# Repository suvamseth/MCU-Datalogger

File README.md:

<div align="center">

# **MCU Datalogger**
### A minimal MCU-based datalogger built in KiCad  

<p>
  <kbd style="padding:3px 14px; font-size:14px; background:#007BFF; color:white;">MCU: ATmega328P-AU</kbd>
  <kbd style="padding:3px 14px; font-size:14px; background:#FF9800; color:white;">RTC: DS3231M</kbd>
  <kbd style="padding:3px 14px; font-size:14px; background:#4CAF50; color:white;">Memory: 24LC1025 × 2</kbd>
  <kbd style="padding:3px 14px; font-size:14px; background:#9C27B0; color:white;">KiCad</kbd>
</p>

</div>

---

## ✨ **Overview**

*A complete KiCad project implementing a simple microcontroller-based datalogger with real-time clock and external memory.*

This project demonstrates how to build a compact datalogger around the **ATmega328P-AU**, with accurate timestamping provided by a **DS3231M RTC** and extended non-volatile storage using **dual 24LC1025 I²C EEPROMs**.  
It is designed as a project for learning KiCad, schematic design, and PCB layout.

--- 

## 🔧 **Key Features**

-  **ATmega328P-AU** microcontroller (Arduino-ready)  
-  **DS3231M RTC** with backup battery support  
-  **2 × 24LC1025 EEPROM** → total **256 KB** storage  
-  Hardware 16 MHz crystal oscillator  
-  UART, SPI, I²C breakout connector  
-  ISP programming support  
-  Status LED    

---
## Final PCB Render

<div align="center">
  
</div>

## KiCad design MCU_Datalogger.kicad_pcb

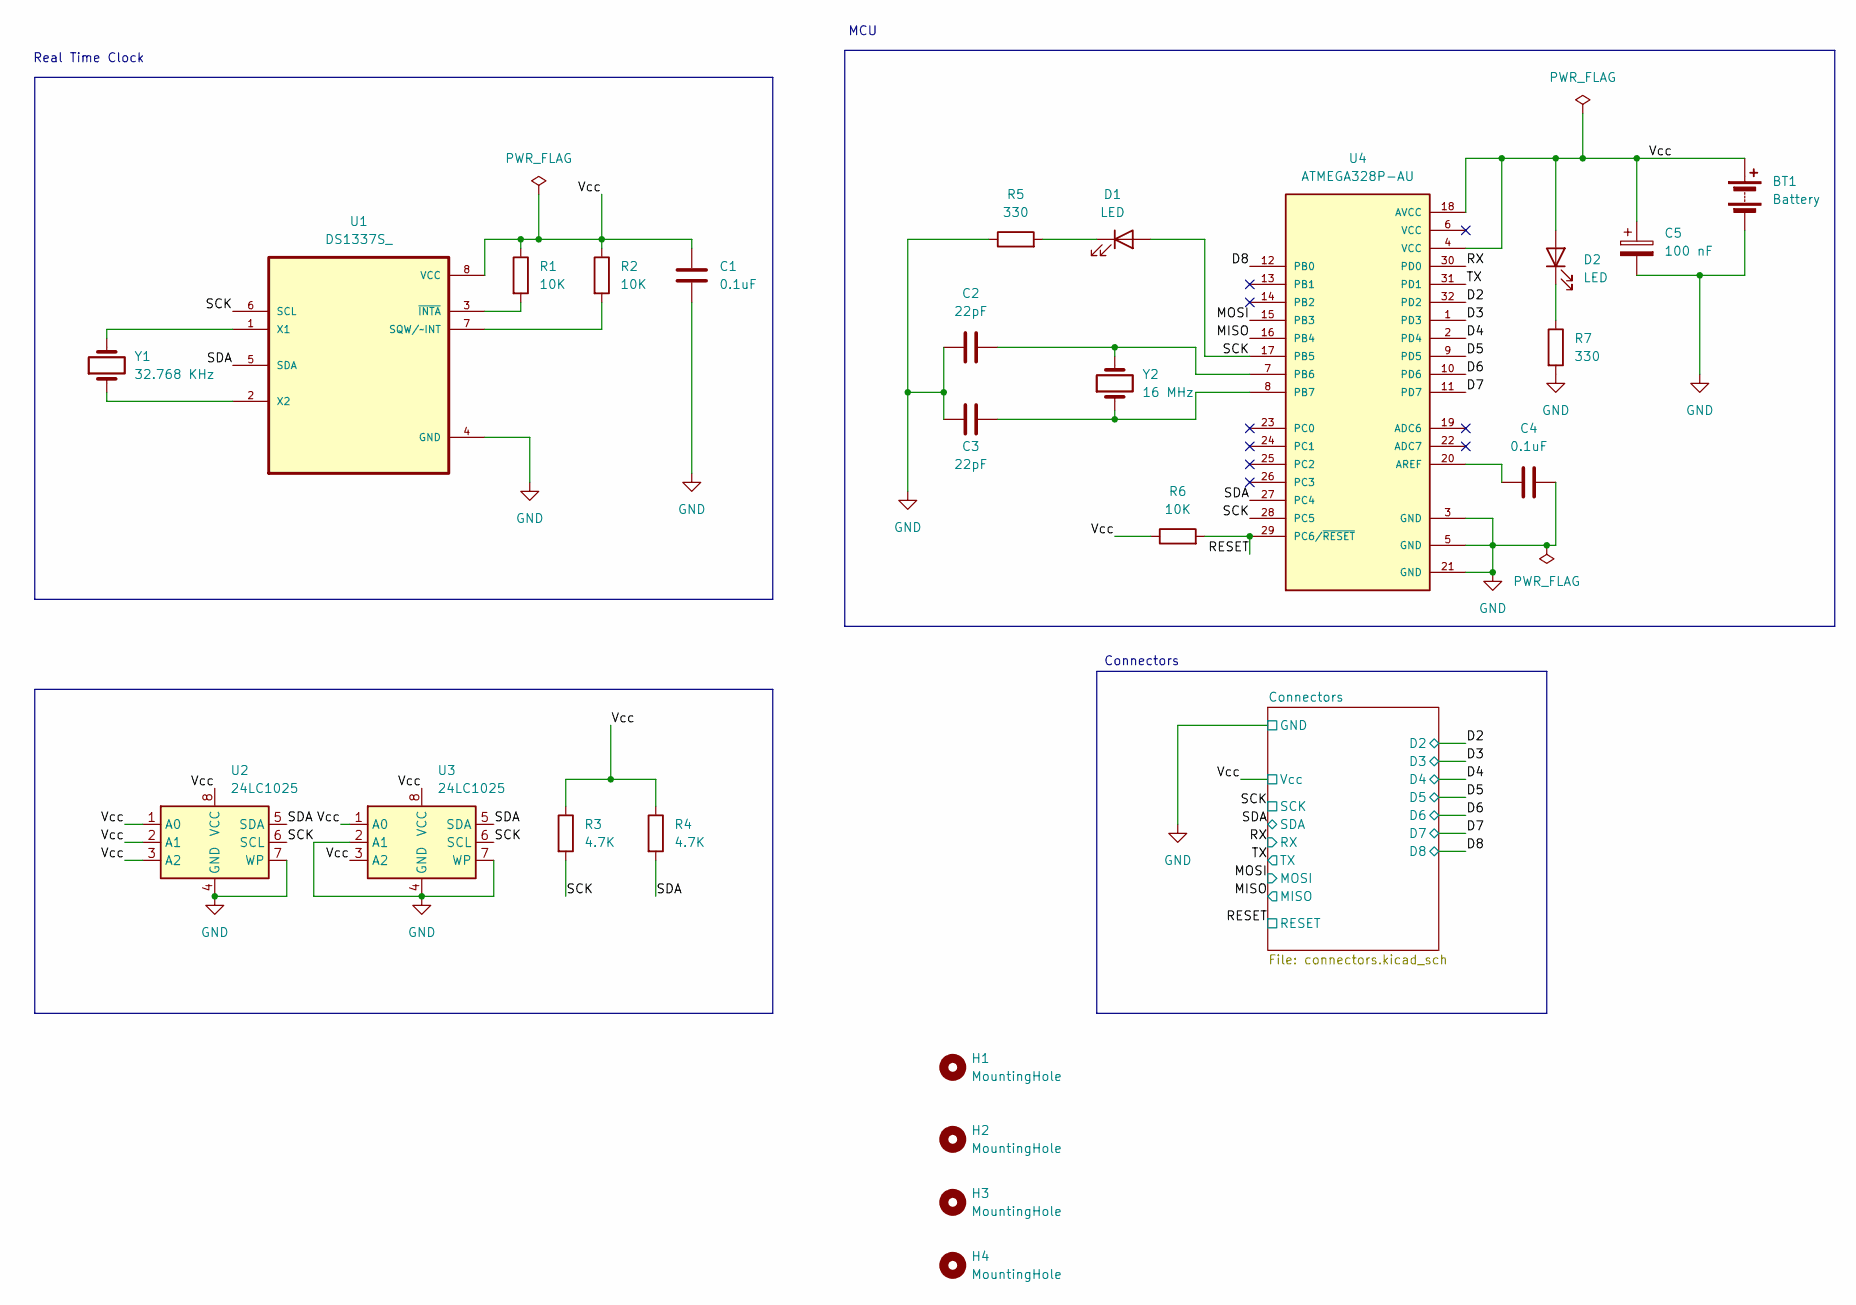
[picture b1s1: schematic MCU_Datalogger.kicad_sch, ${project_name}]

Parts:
BT1: Battery; PinHeader_1x02_P2.54mm_Vertical
C1, C4: 0.1uF; C_0805_2012Metric
C2, C3: 22pF; C_0805_2012Metric
C5: 100 nF; C_0805_2012Metric
D1, D2: LED; LED_0805_2012Metric
H1, H2, H3, H4: MountingHole; MountingHole_2.1mm
R1, R2, R6: 10K; R_0805_2012Metric
R3, R4: 4.7K; R_0805_2012Metric
R5, R7: 330; R_0805_2012Metric
U1: DS1337S_; SOIC127P600X175-8N
U2, U3: 24LC1025; SOIC-8_5.3x5.3mm_P1.27mm
U4: ATMEGA328P-AU; QFP80P900X900X120-32N; PARTREV 8271A
Y1: 32.768 KHz; Crystal_SMD_5032-2Pin_5.0x3.2mm_HandSoldering
Y2: 16 MHz; Crystal_SMD_5032-2Pin_5.0x3.2mm_HandSoldering

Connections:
/D2: U4.32 (PD2); also elsewhere on the board
/D3: U4.1 (PD3); also elsewhere on the board
/D4: U4.2 (PD4); also elsewhere on the board
/D5: U4.9 (PD5); also elsewhere on the board
/D6: U4.10 (PD6); also elsewhere on the board
/D7: U4.11 (PD7); also elsewhere on the board
/D8: U4.12 (PB0); also elsewhere on the board
/MISO: U4.16 (PB4); also elsewhere on the board
/MOSI: U4.15 (PB3); also elsewhere on the board
/RESET: R6.2, U4.29 (PC6/~RESET); also elsewhere on the board
/RX: U4.30 (PD0); also elsewhere on the board
/SCK: D1.2 (A), R3.2, U1.6 (SCL), U2.6 (SCL), U3.6 (SCL), U4.17 (PB5), U4.28 (PC5); also elsewhere on the board
/SDA: R4.2, U1.5 (SDA), U2.5 (SDA), U3.5 (SDA), U4.27 (PC4); also elsewhere on the board
/TX: U4.31 (PD1); also elsewhere on the board
GND: BT1.2 (-), C1.2, C2.1, C3.2, C4.2, C5.2, R5.1, R7.2, U1.4 (GND), U2.4 (GND), U2.7 (WP), U3.2 (A1), U3.4 (GND), U3.7 (WP), U4.3 (GND), U4.5 (GND), U4.21 (GND); also elsewhere on the board
unnamed: D1.1 (K), R5.2
unnamed: D2.1 (K), R7.1
unnamed: R2.2, U1.7 (SQW/~INT)
unnamed: U1.1 (X1), Y1.2
unnamed: U1.2 (X2), Y1.1
unnamed: R1.2, U1.3 (~INTA)
unnamed: C4.1, U4.20 (AREF)
unnamed: C2.2, U4.7 (PB6), Y2.2
unnamed: C3.1, U4.8 (PB7), Y2.1

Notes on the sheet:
Real Time Clock
Connectors
MCU

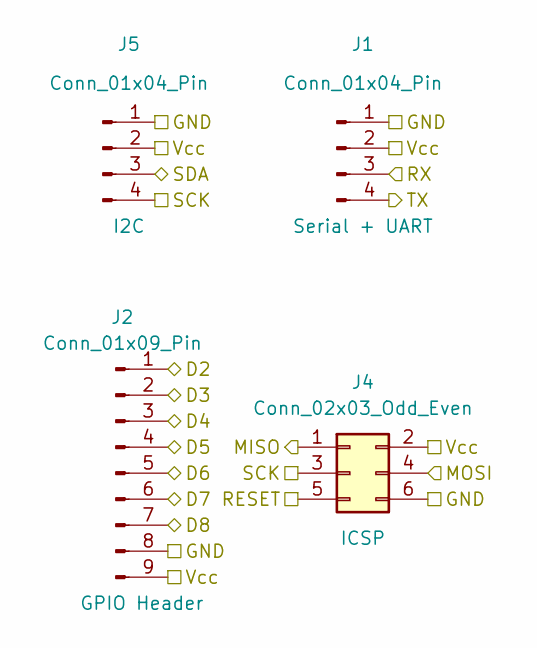
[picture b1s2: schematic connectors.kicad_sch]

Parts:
J1, J5: Conn_01x04_Pin; PinHeader_1x04_P2.54mm_Vertical
J2: Conn_01x09_Pin; PinHeader_1x09_P2.54mm_Vertical
J4: Conn_02x03_Odd_Even; PinHeader_2x03_P2.54mm_Vertical

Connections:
/D2: J2.1; also elsewhere on the board
/D3: J2.2; also elsewhere on the board
/D4: J2.3; also elsewhere on the board
/D5: J2.4; also elsewhere on the board
/D6: J2.5; also elsewhere on the board
/D7: J2.6; also elsewhere on the board
/D8: J2.7; also elsewhere on the board
/MISO: J4.1; also elsewhere on the board
/MOSI: J4.4; also elsewhere on the board
/RESET: J4.5; also elsewhere on the board
/RX: J1.3; also elsewhere on the board
/SCK: J4.3, J5.4; also elsewhere on the board
/SDA: J5.3; also elsewhere on the board
/TX: J1.4; also elsewhere on the board
GND: J1.1, J2.8, J4.6, J5.1; also elsewhere on the board

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
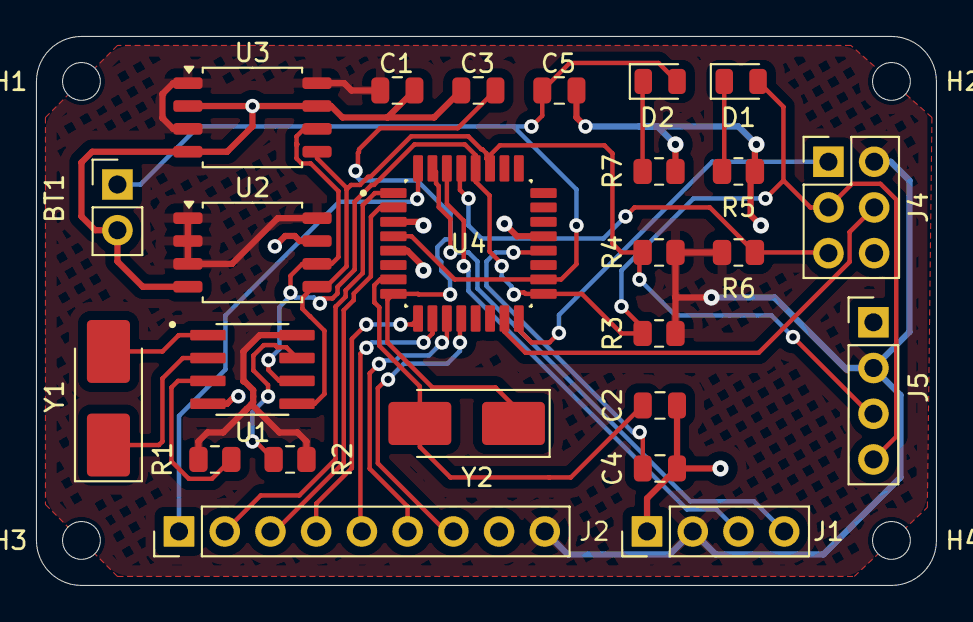
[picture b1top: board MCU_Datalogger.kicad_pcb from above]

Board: 2 copper layers, 50.0 x 30.5 mm, 29 parts (0 on the bottom side), 26 nets.

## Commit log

2025-07-31 Setup of EEschema
2025-07-31 Update .gitignore for KiCad project
2025-07-31 Apply .gitignore to clean tracked files
2025-08-01 minor modification in .gitignore
2025-08-02 Change location of symbols
2025-08-02 Values Added
2025-08-02 Problems in connectors fixed
2025-08-02 Symbol to Footprint Association
2025-08-02 Wiring done
2025-08-02 gnd and vcc net class changed
2025-08-02 completed comments
2025-08-02 Problem in 9 pin connector
2025-08-02 Setup PCBnew
2025-08-02 Completed placement of component on pcb
2025-08-03 PCB Editing Complete
2025-08-03 2Layer pcb done
2025-08-03 PCB Routing Done
2025-12-01 Documentation and Assets updated
